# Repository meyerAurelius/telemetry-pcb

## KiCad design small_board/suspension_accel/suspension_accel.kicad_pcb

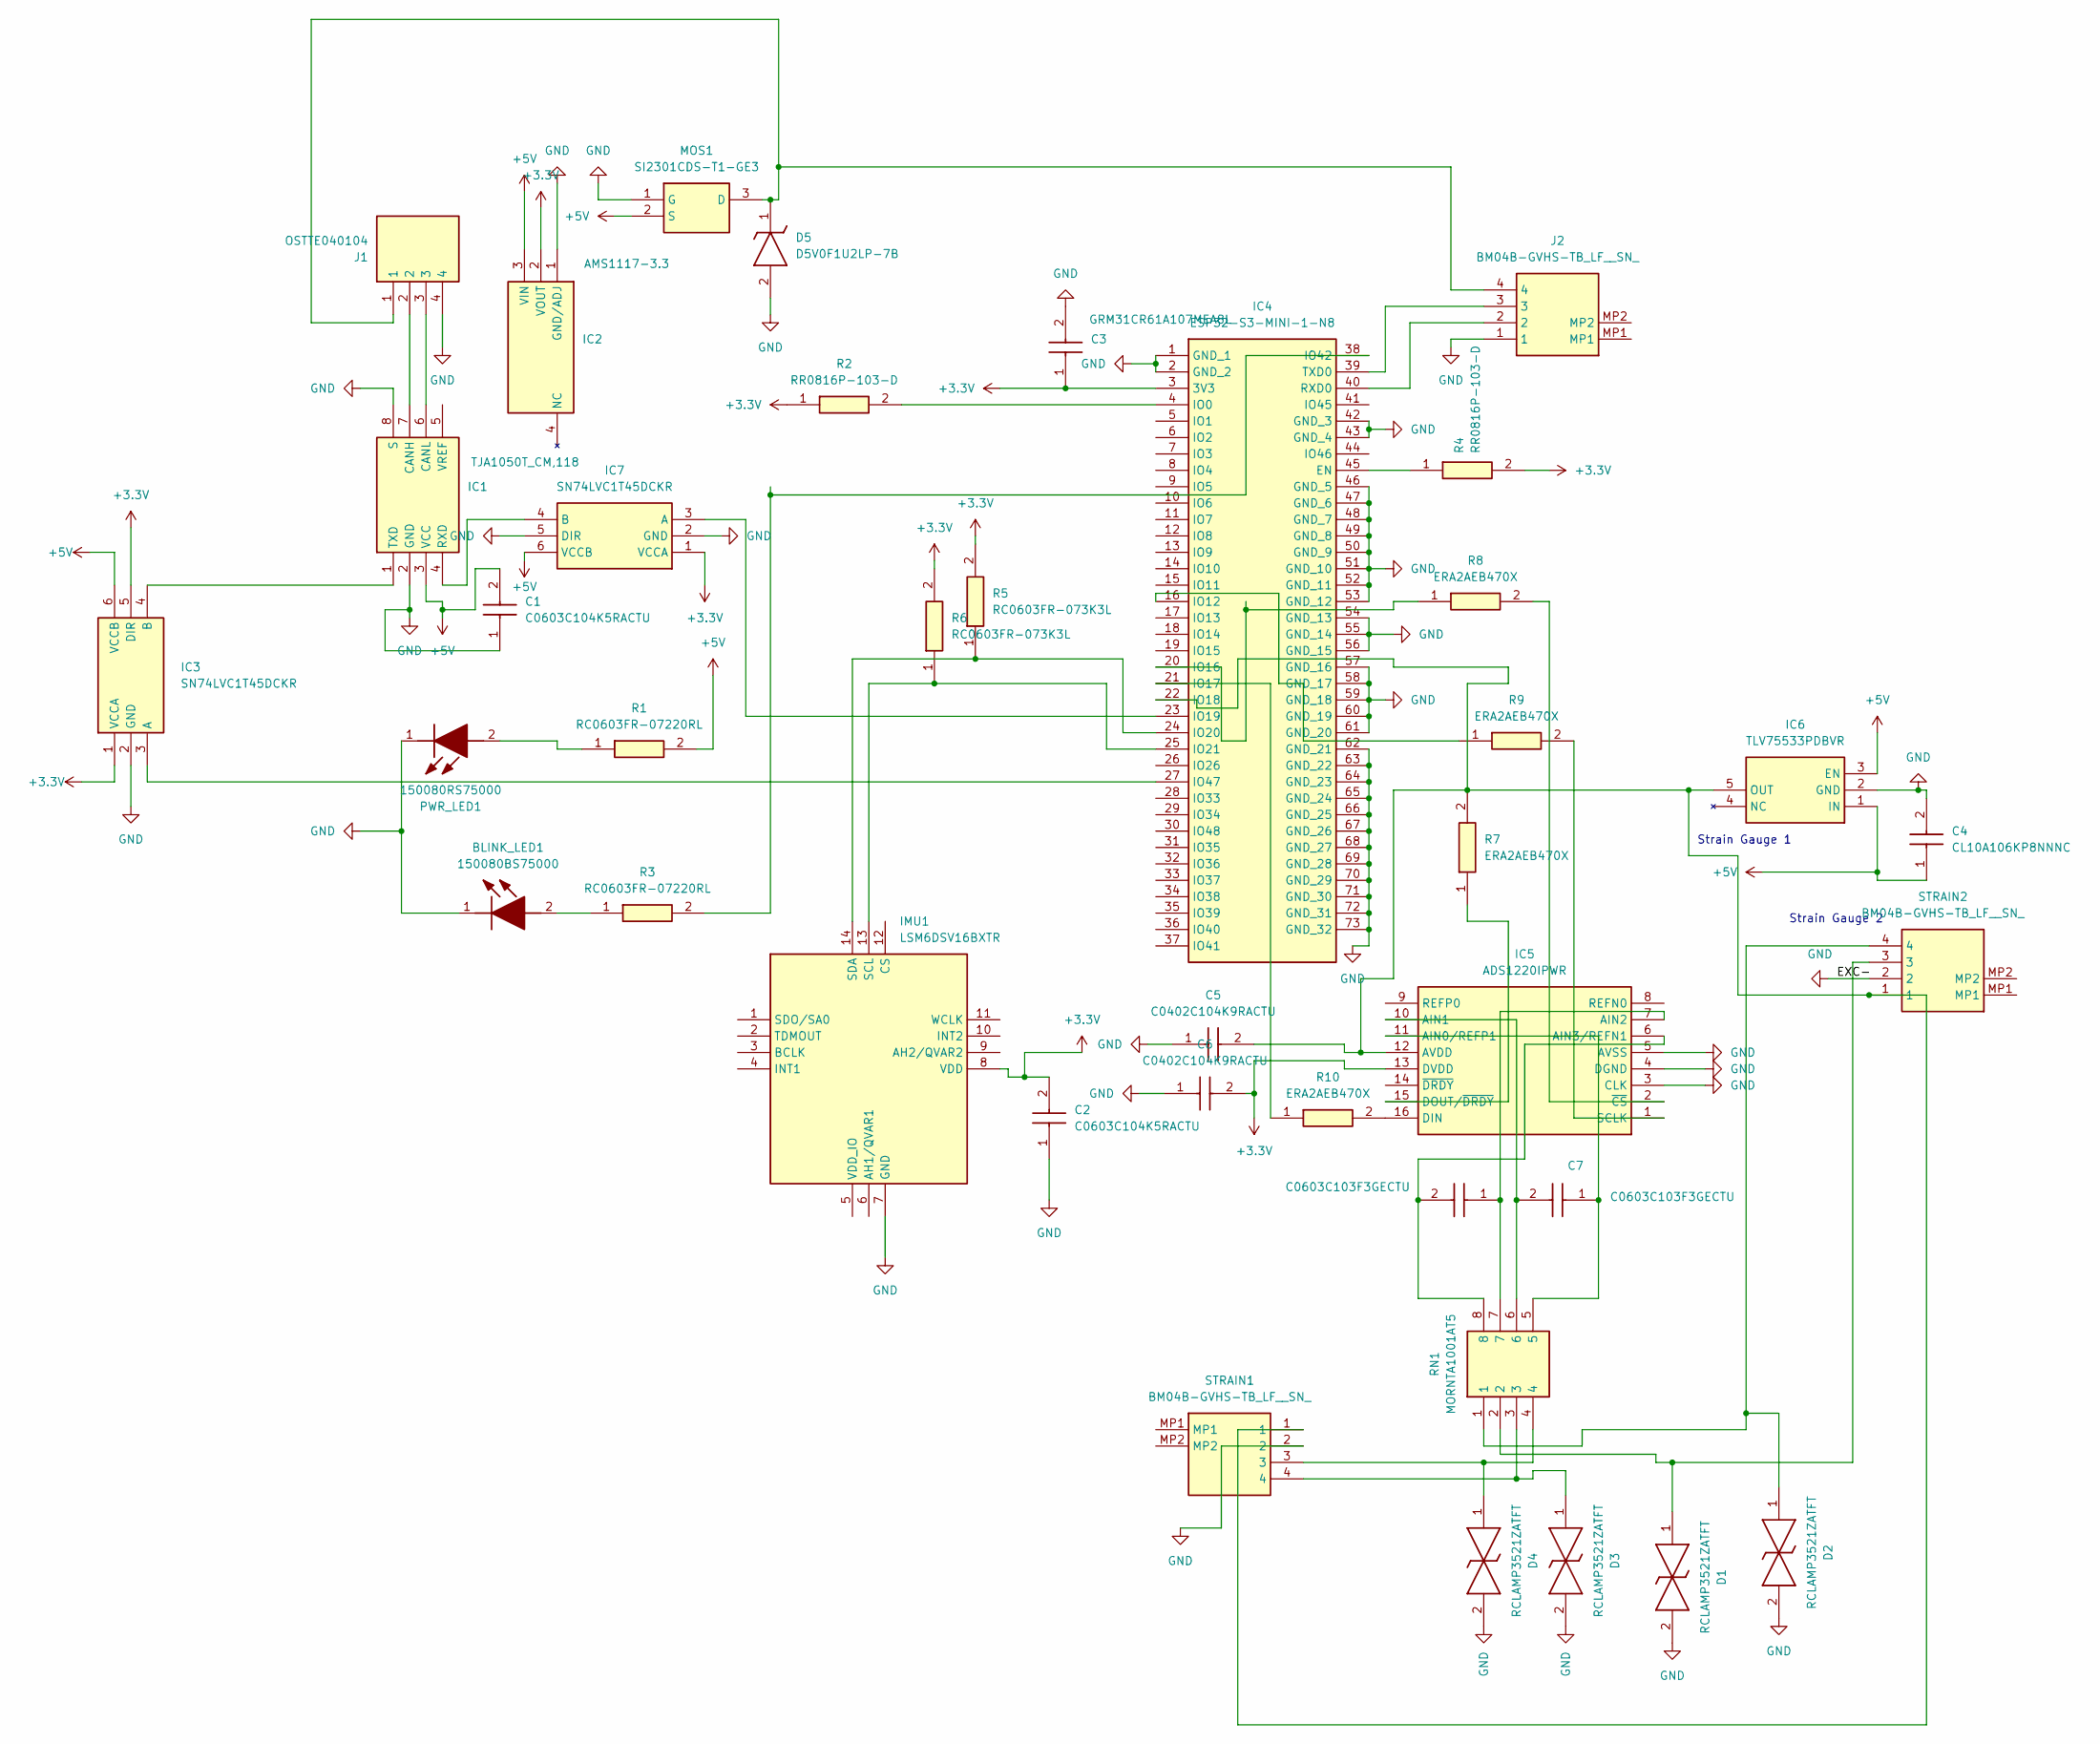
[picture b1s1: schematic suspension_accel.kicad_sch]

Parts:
BLINK_LED1: 150080BS75000; LEDC2012X70N; Manufacturer_Part_Number 150080BS75000; Mouser Part Number 710-150080BS75000
C1, C2: C0603C104K5RACTU; C0603; Manufacturer_Part_Number C0603C104K5RACTU; Mouser Part Number 80-C0603C104K5R
C3: GRM31CR61A107MEA8L; GRM31x; Manufacturer_Part_Number GRM31CR61A107MEA8L; Mouser Part Number 81-GRM31CR61A107MA8L
C4: CL10A106KP8NNNC; CAPC1608X90N; Manufacturer_Part_Number CL10A106KP8NNNC; Mouser Part Number 187-CL10A106KP8NNNC
C5, C6: C0402C104K9RACTU; C0402C104J4RACTU; Manufacturer_Part_Number C0402C104K9RACTU; Mouser Part Number 80-C0402C104K9R
C7, C8: C0603C103F3GECTU; CAPC1608X87N; Manufacturer_Part_Number C0603C103F3GECTU; Mouser Part Number 80-C0603C103F3GEC
D1, D2, D3, D4: RCLAMP3521ZATFT; Manufacturer_Part_Number RCLAMP3521ZATFT; Mouser Part Number 947-RCLAMP3521ZATFT
D5: D5V0F1U2LP-7B; D5V0F1U2LP7B; Manufacturer_Part_Number D5V0F1U2LP-7B; Mouser Part Number 621-D5V0F1U2LP7B
IC1: TJA1050T_CM,118; SOIC127P600X175-8N; Manufacturer_Part_Number TJA1050T/CM,118; Mouser Part Number 771-TJA1050T/CM118
IC2: AMS1117-3.3; SOT229P700X180-4N; Manufacturer_Part_Number AMS1117-3.3
IC3, IC7: SN74LVC1T45DCKR; SOT65P210X110-6N; Manufacturer_Part_Number SN74LVC1T45DCKR; Mouser Part Number 595-SN74LVC1T45DCKR
IC4: ESP32-S3-MINI-1-N8; ESP32S3MINI1N8; Manufacturer_Part_Number ESP32-S3-MINI-1-N8; Mouser Part Number 356-ESP32-S3-MINI1N8
IC5: ADS1220IPWR; SOP65P640X120-16N; Manufacturer_Part_Number ADS1220IPWR; Mouser Part Number 595-ADS1220IPWR
IC6: TLV75533PDBVR; SOT95P280X145-5N; Manufacturer_Part_Number TLV75533PDBVR; Mouser Part Number 595-TLV75533PDBVR
IMU1: LSM6DSV16BXTR; Manufacturer_Part_Number LSM6DSV16BXTR; Mouser Part Number 511-LSM6DSV16BXTR
J1: OSTTE040104; Manufacturer_Part_Number OSTTE040104
J2: BM04B-GVHS-TB_LF__SN_; BM04BGVHSTBLFSN; Manufacturer_Part_Number BM04B-GVHS-TB(LF)(SN)
MOS1: SI2301CDS-T1-GE3; SOT95P237X112-3N; Manufacturer_Part_Number SI2301CDS-T1-GE3; Mouser Part Number 781-SI2301CDS-T1-GE3
PWR_LED1: 150080RS75000; LEDC2012X70N; Manufacturer_Part_Number 150080RS75000; Mouser Part Number 710-150080RS75000
R1, R3: RC0603FR-07220RL; RESC1608X55N; Manufacturer_Part_Number RC0603FR-07220RL; Mouser Part Number 603-RC0603FR-07220RL
R2, R4: RR0816P-103-D; RESC1608X60N; Manufacturer_Part_Number RR0816P-103-D; Mouser Part Number 754-RR0816P-103D
R5, R6: RC0603FR-073K3L; RESC1608X55N; Manufacturer_Part_Number RC0603FR-073K3L; Mouser Part Number 603-RC0603FR-073K3L
R7, R8, R9, R10: ERA2AEB470X; ERA2AED122X; Manufacturer_Part_Number ERA2AEB470X
RN1: MORNTA1001AT5; Manufacturer_Part_Number MORNTA1001AT5; Mouser Part Number 71-MORNTA1001AT5
STRAIN1, STRAIN2: BM04B-GVHS-TB_LF__SN_; BM04BGVHSTBLFSN; Manufacturer_Part_Number BM04B-GVHS-TB(LF)(SN)

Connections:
+3.3V: C2.2, C3.1, C6.2, IC2.2 (VOUT), IC3.1 (VCCA), IC3.5 (DIR), IC4.3 (3V3), IC5.13 (DVDD), IC7.1 (VCCA), IMU1.8 (VDD), R2.1 (R1), R4.2 (R2), R5.2, R6.2
+5V: C1.2, C4.1, IC1.3 (VCC), IC2.3 (VIN), IC3.6 (VCCB), IC6.1 (IN), IC6.3 (EN), IC7.6 (VCCB), MOS1.2 (S), R1.2
GND: BLINK_LED1.1 (K), C1.1, C2.1, C3.2, C4.2, C5.1, C6.1, D1.2, D2.2, D3.2, D4.2, D5.2 (A), IC1.2 (GND), IC1.8 (S), IC2.1 (GND/ADJ), IC3.2 (GND), IC4.1 (GND_1), IC4.2 (GND_2), IC4.42 (GND_3), IC4.43 (GND_4), IC4.46 (GND_5), IC4.47 (GND_6), IC4.48 (GND_7), IC4.49 (GND_8), IC4.50 (GND_9), IC4.51 (GND_10), IC4.52 (GND_11), IC4.53 (GND_12), IC4.54 (GND_13), IC4.55 (GND_14), IC4.56 (GND_15), IC4.57 (GND_16), IC4.58 (GND_17), IC4.59 (GND_18), IC4.60 (GND_19), IC4.61 (GND_20), IC4.62 (GND_21), IC4.63 (GND_22), IC4.64 (GND_23), IC4.65 (GND_24), IC4.66 (GND_25), IC4.67 (GND_26), IC4.68 (GND_27), IC4.69 (GND_28), IC4.70 (GND_29), IC4.71 (GND_30), IC4.72 (GND_31), IC4.73 (GND_32), IC5.3 (CLK), IC5.4 (DGND), IC5.5 (AVSS), IC6.2 (GND), IC7.2 (GND), IC7.5 (DIR), IMU1.7 (GND), J1.4, J2.1, MOS1.1 (G), PWR_LED1.1 (K), STRAIN1.2, STRAIN2.2
unnamed: BLINK_LED1.2 (A), R3.1
unnamed: D1.1, RN1.2, STRAIN2.3
unnamed: D2.1, RN1.1, STRAIN2.4
unnamed: D3.1, RN1.3, STRAIN1.4
unnamed: D4.1, RN1.4, STRAIN1.3
unnamed: D5.1 (K), J1.1, J2.4, MOS1.3 (D)
unnamed: IC1.7 (CANH), J1.2
unnamed: IC1.6 (CANL), J1.3
unnamed: IC1.4 (RXD), IC7.4 (B)
unnamed: IC1.1 (TXD), IC3.4 (B)
unnamed: IC3.3 (A), IC4.27 (IO47)
unnamed: IC4.45 (EN), R4.1 (R1)
unnamed: IC4.4 (IO0), R2.2 (R2)
unnamed: IC4.16 (IO12), R9.1
unnamed: IC4.20 (IO16), R8.1
unnamed: IC4.21 (IO17), R10.1
unnamed: C5.2, IC4.22 (IO18), IC5.12 (AVDD), IC6.5 (OUT), R7.2, STRAIN1.1, STRAIN2.1
unnamed: IC4.23 (IO19), IC7.3 (A)
unnamed: IC4.24 (IO20), IMU1.14 (SDA), R5.1
unnamed: IC4.25 (IO21), IMU1.13 (SCL), R6.1
unnamed: IC4.38 (IO42), R3.2
unnamed: IC4.40 (RXD0), J2.2
unnamed: IC4.39 (TXD0), J2.3
unnamed: C7.1, IC5.11 (AIN0/REFP1), RN1.5
unnamed: C7.2, IC5.10 (AIN1), RN1.6
unnamed: C8.1, IC5.7 (AIN2), RN1.7
unnamed: C8.2, IC5.6 (AIN3/REFN1), RN1.8
unnamed: IC5.16 (DIN), R10.2
unnamed: IC5.15 (DOUT/~DRDY), R7.1
unnamed: IC5.1 (SCLK), R9.2
unnamed: IC5.2 (~CS), R8.2
unnamed: PWR_LED1.2 (A), R1.1

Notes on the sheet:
Strain Gauge 2
Strain Gauge 1

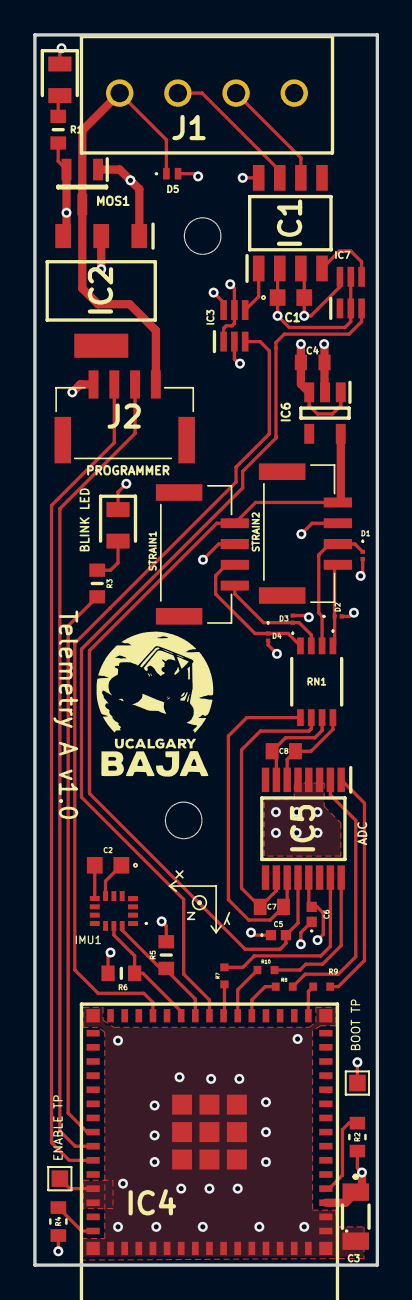
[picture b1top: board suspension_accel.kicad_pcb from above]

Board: 4 copper layers, 20.6 x 74.0 mm, 39 parts (0 on the bottom side), 35 nets.

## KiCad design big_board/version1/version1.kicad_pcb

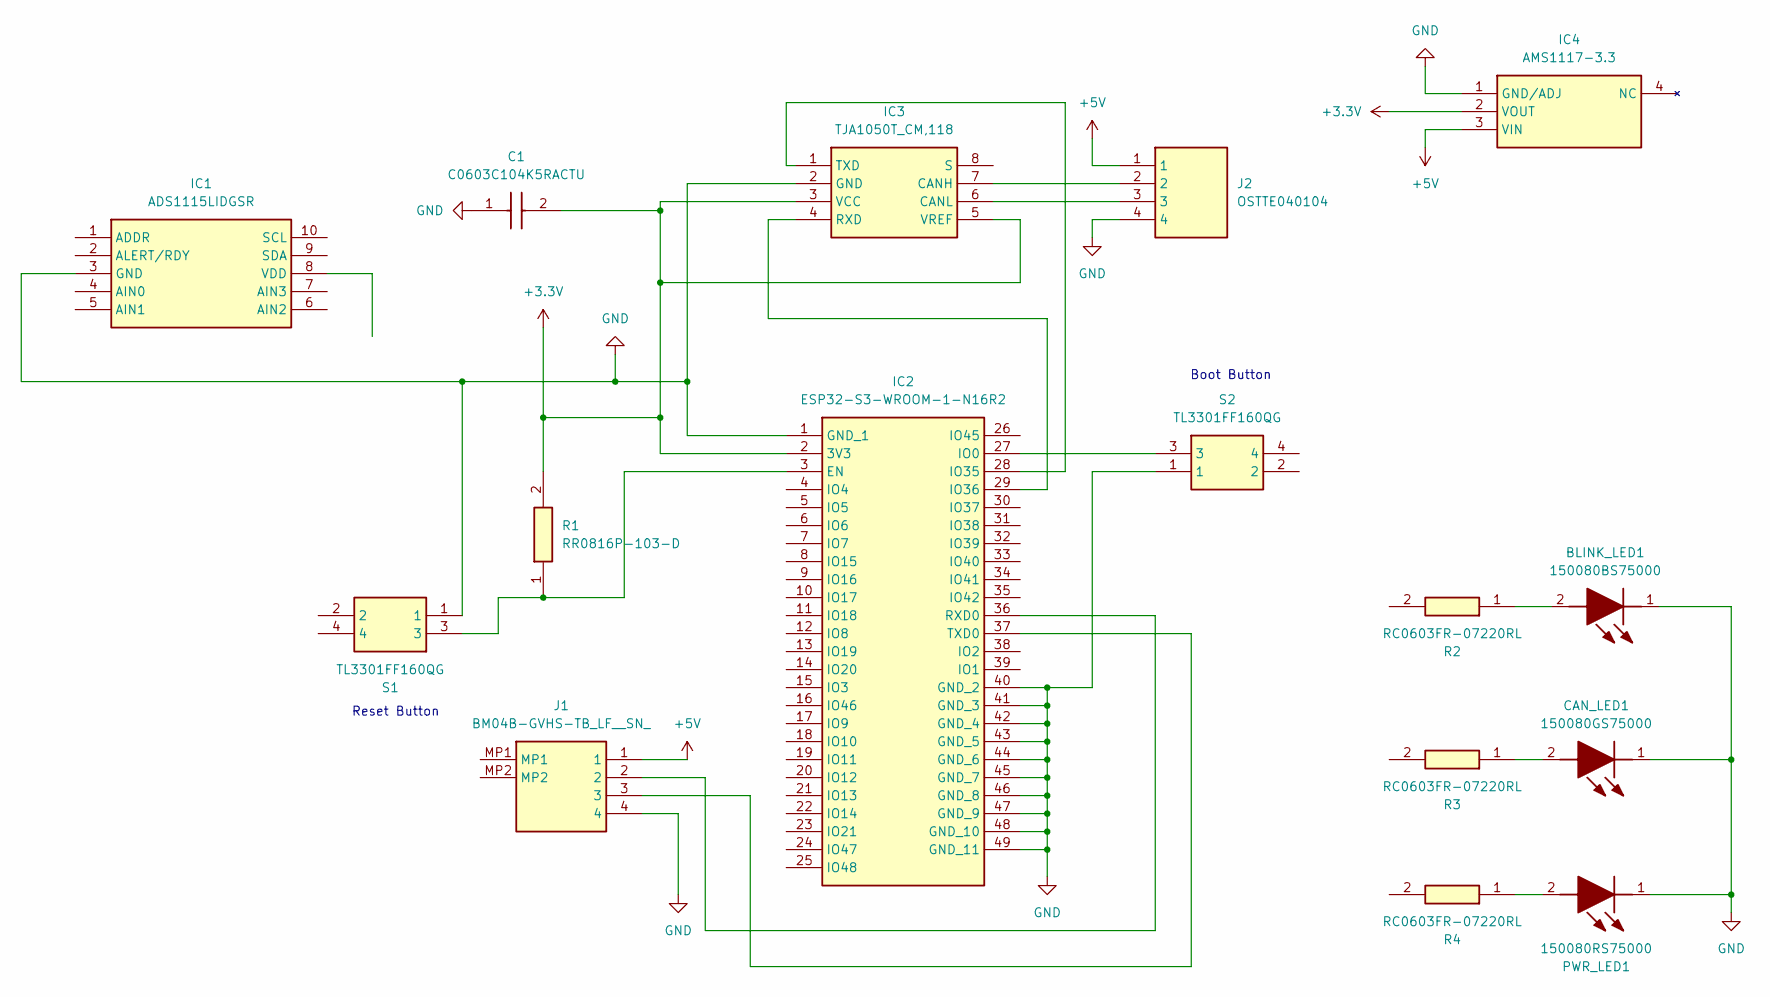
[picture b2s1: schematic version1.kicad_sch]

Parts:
BLINK_LED1: 150080BS75000; LEDC2012X70N; Manufacturer_Part_Number 150080BS75000; Mouser Part Number 710-150080BS75000
C1: C0603C104K5RACTU; C0603; Manufacturer_Part_Number C0603C104K5RACTU; Mouser Part Number 80-C0603C104K5R
CAN_LED1: 150080GS75000; LEDM2012X70N; Manufacturer_Part_Number 150080GS75000; Mouser Part Number 710-150080GS75000
IC1: ADS1115LIDGSR; SOP50P490X110-10N; Manufacturer_Part_Number ADS1115LIDGSR; Mouser Part Number 595-ADS1115LIDGSR
IC2: ESP32-S3-WROOM-1-N16R2; ESP32S3WROOM1N16R2; Manufacturer_Part_Number ESP32-S3-WROOM-1-N16R2; Mouser Part Number 356-ESP32S3WRM1N16R2
IC3: TJA1050T_CM,118; SOIC127P600X175-8N; Manufacturer_Part_Number TJA1050T/CM,118; Mouser Part Number 771-TJA1050T/CM118
IC4: AMS1117-3.3; SOT229P700X180-4N; Manufacturer_Part_Number AMS1117-3.3
J1: BM04B-GVHS-TB_LF__SN_; BM04BGVHSTBLFSN; Manufacturer_Part_Number BM04B-GVHS-TB(LF)(SN)
J2: OSTTE040104; Manufacturer_Part_Number OSTTE040104
PWR_LED1: 150080RS75000; LEDC2012X70N; Manufacturer_Part_Number 150080RS75000; Mouser Part Number 710-150080RS75000
R1: RR0816P-103-D; RESC1608X60N; Manufacturer_Part_Number RR0816P-103-D; Mouser Part Number 754-RR0816P-103D
R2, R3, R4: RC0603FR-07220RL; RESC1608X55N; Manufacturer_Part_Number RC0603FR-07220RL; Mouser Part Number 603-RC0603FR-07220RL
S1, S2: TL3301FF160QG; Manufacturer_Part_Number TL3301FF160QG; Mouser Part Number 612-TL3301F

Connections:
+3.3V: C1.2, IC2.2 (3V3), IC3.3 (VCC), IC3.5 (VREF), IC4.2 (VOUT), R1.2 (R2)
+5V: IC4.3 (VIN), J1.1, J2.1
GND: BLINK_LED1.1 (K), C1.1, CAN_LED1.1 (K), IC1.3 (GND), IC2.1 (GND_1), IC2.40 (GND_2), IC2.41 (GND_3), IC2.42 (GND_4), IC2.43 (GND_5), IC2.44 (GND_6), IC2.45 (GND_7), IC2.46 (GND_8), IC2.47 (GND_9), IC2.48 (GND_10), IC2.49 (GND_11), IC3.2 (GND), IC4.1 (GND/ADJ), J1.4, J2.4, PWR_LED1.1 (K), S1.1, S2.1
unnamed: BLINK_LED1.2 (A), R2.1
unnamed: CAN_LED1.2 (A), R3.1
unnamed: IC2.3 (EN), R1.1 (R1), S1.3
unnamed: IC2.27 (IO0), S2.3
unnamed: IC2.28 (IO35), IC3.1 (TXD)
unnamed: IC2.29 (IO36), IC3.4 (RXD)
unnamed: IC2.36 (RXD0), J1.2
unnamed: IC2.37 (TXD0), J1.3
unnamed: IC3.7 (CANH), J2.2
unnamed: IC3.6 (CANL), J2.3
unnamed: PWR_LED1.2 (A), R4.1

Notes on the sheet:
Boot Button
Reset Button

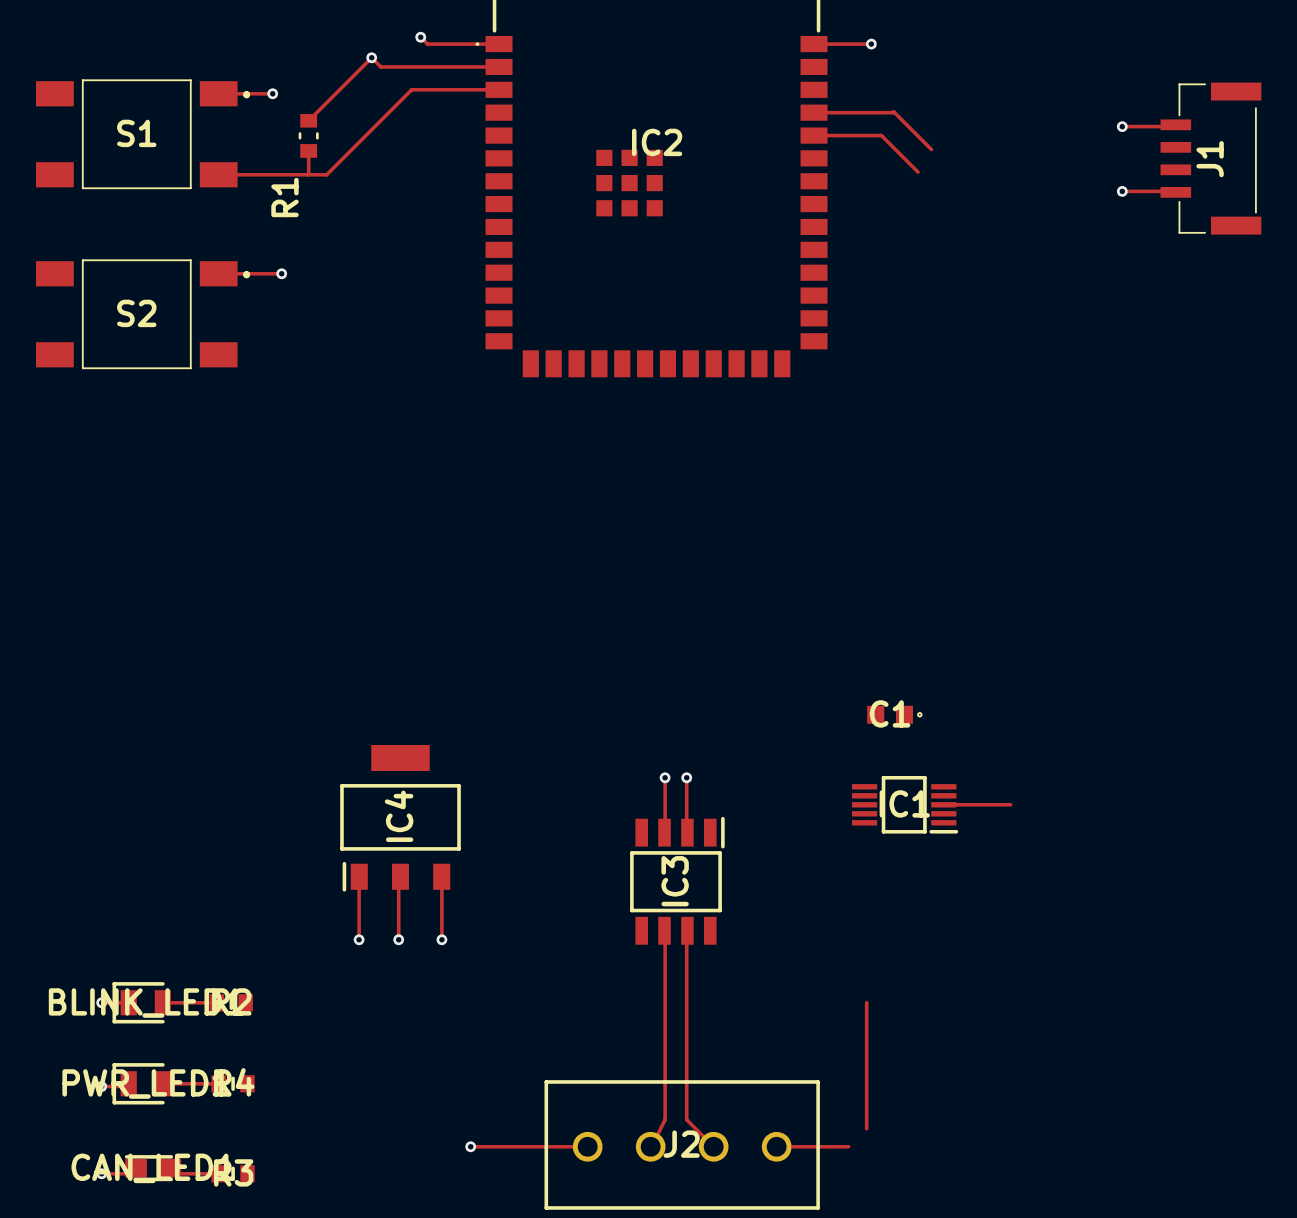
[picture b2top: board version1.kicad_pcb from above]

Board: 4 copper layers, 16 parts (0 on the bottom side), 14 nets.

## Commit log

2026-01-29 placed initial components, leds, etc... Started working on routing the tracks
2026-01-31 added voltage regulator
2026-02-01 reorganized structure for two PCBs
2026-02-01 Recovered
2026-02-01 Basic creation of the shematic and pcb
2026-02-02 small_board work, added buttons
2026-02-05 added MPU, smaller buttons, started routing
2026-02-05 generated pcb step file
2026-02-07 before branching
2026-02-07 added strain gauge adc, strain gauge ldo, comp components and headers for load cell hookups
2026-02-09 Added rev polarity protection, ads1220, routed, tja1050 level shifter, etc...
2026-02-14 moved adc to provide space for filters
2026-02-14 not much changed
2026-02-16 finished filter work, rerounted connection, bus level shifters connected, blink led connected, etc...
2026-02-21 add wiring_assembly directory
2026-02-21 added matched resistor network
2026-02-21 Update car wiring diagram
2026-02-21 started laying out final components
2026-02-27 added ground pours and routed adc inputs
2026-02-27 finished routing, added logo, widened board for DRC compliance
2026-02-27 Added copper layers for each net, adding cool slikscreen stuff
2026-02-28 added supply line TVS
2026-03-01 prepared for manufacturing first iter
2026-03-01 created finalized step file
2026-03-02 spaced out routing a bit
2026-03-07 maintenance
2026-03-07 created new version for new dimensions
